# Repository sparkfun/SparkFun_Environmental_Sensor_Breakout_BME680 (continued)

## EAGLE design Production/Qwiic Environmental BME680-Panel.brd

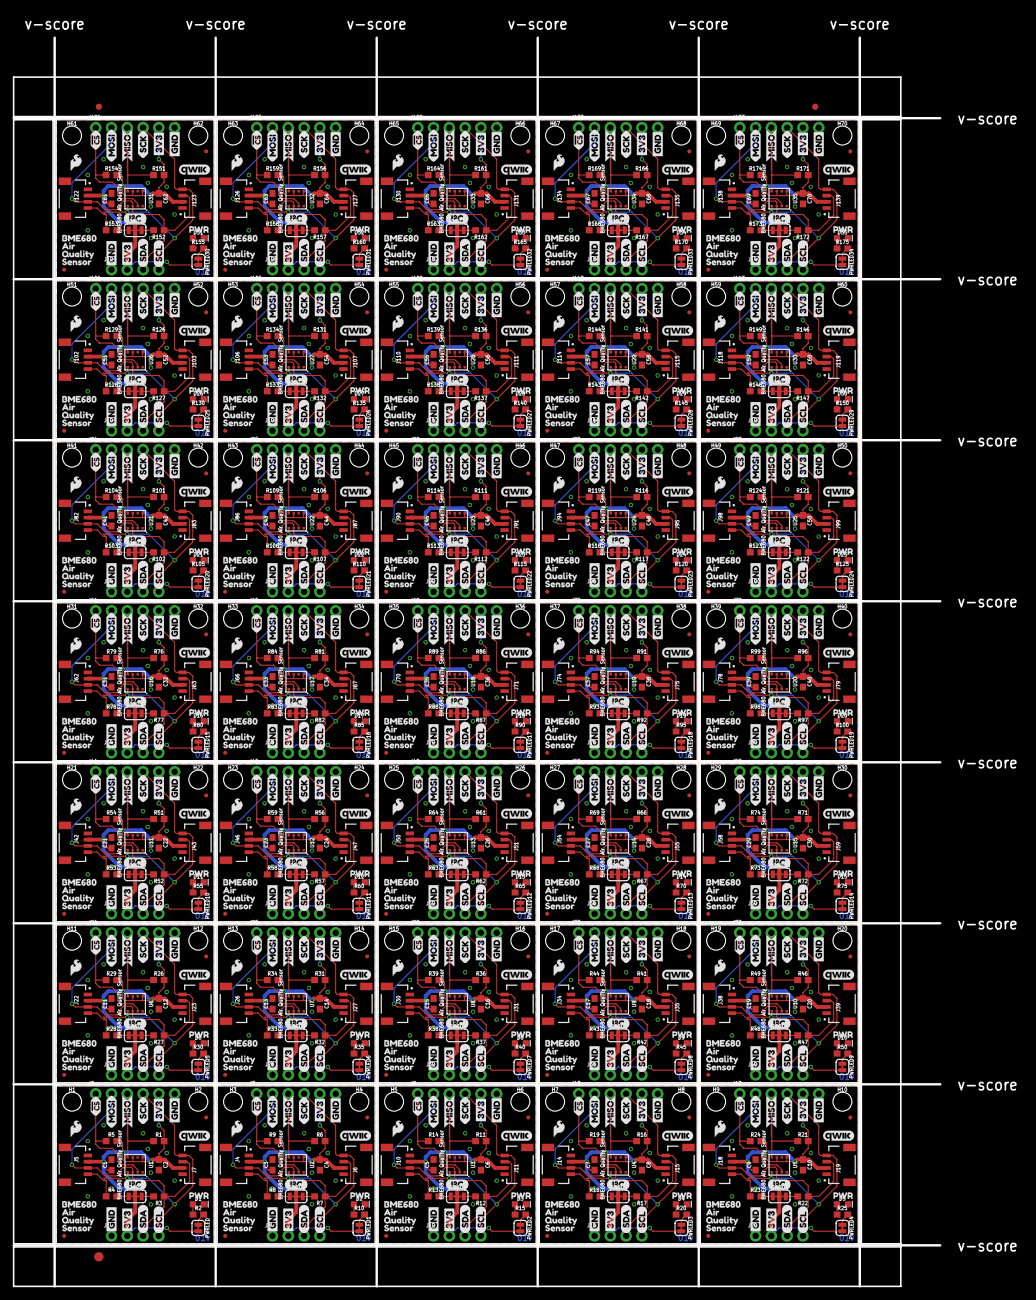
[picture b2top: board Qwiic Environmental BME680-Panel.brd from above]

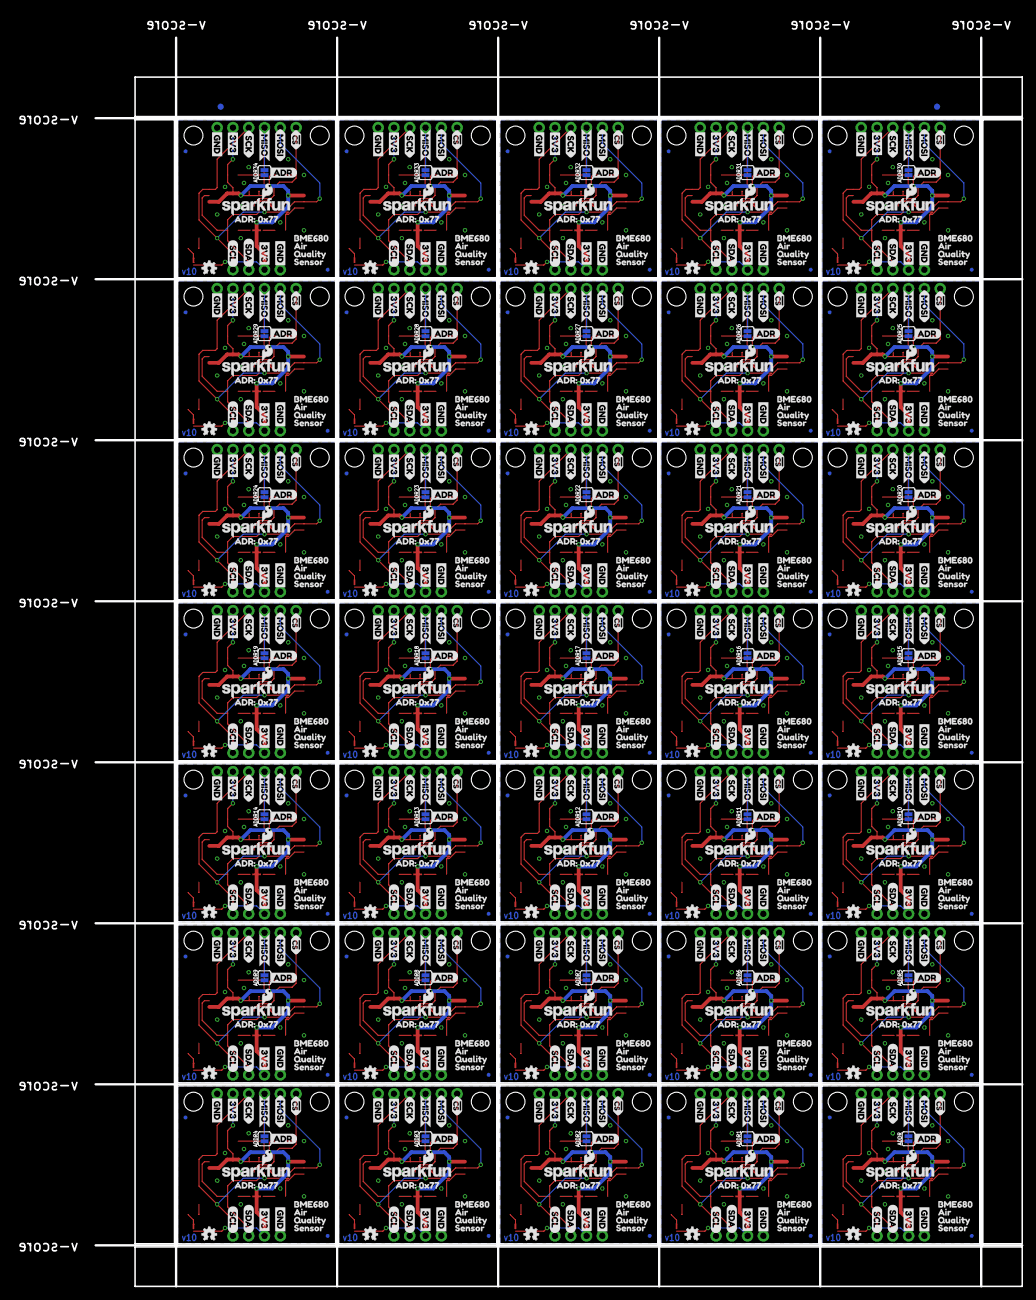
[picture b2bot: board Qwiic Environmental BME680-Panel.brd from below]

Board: 2 copper layers, 149.1 x 200.9 mm, 2070 parts (737 on the bottom side), 350 nets.

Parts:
ADDR, ADDR1, ADDR2, ADDR3, ADDR4, ADDR5, ADDR6, ADDR7, ADDR8, ADDR9, ADDR10, ADDR11, ADDR12, ADDR13, ADDR14, ADDR15, ADDR16, ADDR17, ADDR18, ADDR19, ADDR20, ADDR21, ADDR22, ADDR23, ADDR24, ADDR25, ADDR26, ADDR27, ADDR28, ADDR29, ADDR30, ADDR31, ADDR32, ADDR33, ADDR34: JUMPER-SMT_2_NO_SILK; SMT-JUMPER_2_NO_SILK
C1, C2, C3, C4, C5, C6, C7, C8, C9, C10, C11, C12, C13, C14, C15, C16, C17, C18, C19, C20, C21, C22, C23, C24, C25, C26, C27, C28, C29, C30, C31, C32, C33, C34, C35, C36, C37, C38, C39, C40, C41, C42, C43, C44, C45, C46, C47, C48, C49, C50, C51, C52, C53, C54, C55, C56, C57, C58, C59, C60, C61, C62, C63, C64, C65, C66, C67, C68, C69, C70: 0.1uF; 0603
D1, D2, D3, D4, D5, D6, D7, D8, D9, D10, D11, D12, D13, D14, D15, D16, D17, D18, D19, D20, D21, D22, D23, D24, D25, D26, D27, D28, D29, D30, D31, D32, D33, D34, D35: RED; LED-0603
E$1, E$2, E$3, E$4: FIDUCIAL-1X2
E$5: FIDUCIAL-1.5X3
FD1, FD2, FD3, FD4, FD5, FD6, FD7, FD8, FD9, FD10, FD11, FD12, FD13, FD14, FD15, FD16, FD17, FD18, FD19, FD20, FD21, FD22, FD23, FD24, FD25, FD26, FD27, FD28, FD29, FD30, FD31, FD32, FD33, FD34, FD35, FD36, FD37, FD38, FD39, FD40, FD41, FD42, FD43, FD44, FD45, FD46, FD47, FD48, FD49, FD50, FD51, FD52, FD53, FD54, FD55, FD56, FD57, FD58, FD59, FD60, FD61, FD62, FD63, FD64, FD65, FD66, FD67, FD68, FD69, FD70, FD71, FD72, FD73, FD74, FD75, FD76, FD77, FD78, FD79, FD80, FD81, FD82, FD83, FD84, FD85, FD86, FD87, FD88, FD89, FD90, FD91, FD92, FD93, FD94, FD95, FD96, FD97, FD98, FD99, FD100, FD101, FD102, FD103, FD104, FD105, FD106, FD107, FD108, FD109, FD110, FD111, FD112, FD113, FD114, FD115, FD116, FD117, FD118, FD119, FD120, FD121, FD122, FD123, FD124, FD125, FD126, FD127, FD128, FD129, FD130, FD131, FD132, FD133, FD134, FD135, FD136, FD137, FD138, FD139, FD140: FIDUCIALUFIDUCIAL; FIDUCIAL-MICRO
H1, H2, H3, H4, H5, H6, H7, H8, H9, H10, H11, H12, H13, H14, H15, H16, H17, H18, H19, H20, H21, H22, H23, H24, H25, H26, H27, H28, H29, H30, H31, H32, H33, H34, H35, H36, H37, H38, H39, H40, H41, H42, H43, H44, H45, H46, H47, H48, H49, H50, H51, H52, H53, H54, H55, H56, H57, H58, H59, H60, H61, H62, H63, H64, H65, H66, H67, H68, H69, H70: STAND-OFFTIGHT; STAND-OFF-TIGHT
I2CPU, I2CPU1, I2CPU2, I2CPU3, I2CPU4, I2CPU5, I2CPU6, I2CPU7, I2CPU8, I2CPU9, I2CPU10, I2CPU11, I2CPU12, I2CPU13, I2CPU14, I2CPU15, I2CPU16, I2CPU17, I2CPU18, I2CPU19, I2CPU20, I2CPU21, I2CPU22, I2CPU23, I2CPU24, I2CPU25, I2CPU26, I2CPU27, I2CPU28, I2CPU29, I2CPU30, I2CPU31, I2CPU32, I2CPU33, I2CPU34: I2C PU; SMT-JUMPER_3_2-NC_TRACE_SILK
J1, J8, J12, J16, J20, J24, J28, J32, J36, J40, J44, J48, J52, J56, J60, J64, J68, J72, J76, J80, J84, J88, J92, J96, J100, J104, J108, J112, J116, J120, J124, J128, J132, J136, J140: I2C; 1X04_NO_SILK
J2, J3, J9, J13, J17, J21, J25, J29, J33, J37, J41, J45, J49, J53, J57, J61, J65, J69, J73, J77, J81, J85, J89, J93, J97, J101, J105, J109, J113, J117, J121, J125, J129, J133, J137: SPI; 1X06_NO_SILK
J4, J5, J6, J7, J10, J11, J14, J15, J18, J19, J22, J23, J26, J27, J30, J31, J34, J35, J38, J39, J42, J43, J46, J47, J50, J51, J54, J55, J58, J59, J62, J63, J66, J67, J70, J71, J74, J75, J78, J79, J82, J83, J86, J87, J90, J91, J94, J95, J98, J99, J102, J103, J106, J107, J110, J111, J114, J115, J118, J119, J122, J123, J126, J127, J130, J131, J134, J135, J138, J139: QWIIC; JST04_1MM_RA
LOGO1, LOGO5, LOGO9, LOGO13, LOGO17, LOGO21, LOGO25, LOGO29, LOGO33, LOGO37, LOGO41, LOGO45, LOGO49, LOGO53, LOGO57, LOGO61, LOGO65, LOGO69, LOGO73, LOGO77, LOGO81, LOGO85, LOGO89, LOGO93, LOGO97, LOGO101, LOGO105, LOGO109, LOGO113, LOGO117, LOGO121, LOGO125, LOGO129, LOGO133, LOGO137: OSHW-LOGOMINI; OSHW-LOGO-MINI
LOGO2, LOGO7, LOGO11, LOGO15, LOGO19, LOGO23, LOGO27, LOGO31, LOGO35, LOGO39, LOGO43, LOGO47, LOGO51, LOGO55, LOGO59, LOGO63, LOGO67, LOGO71, LOGO75, LOGO79, LOGO83, LOGO87, LOGO91, LOGO95, LOGO99, LOGO103, LOGO107, LOGO111, LOGO115, LOGO119, LOGO123, LOGO127, LOGO131, LOGO135, LOGO139: SFE_LOGO_NAME_FLAME.1_INCH; SFE_LOGO_NAME_FLAME_.1
LOGO3, LOGO6, LOGO10, LOGO14, LOGO18, LOGO22, LOGO26, LOGO30, LOGO34, LOGO38, LOGO42, LOGO46, LOGO50, LOGO54, LOGO58, LOGO62, LOGO66, LOGO70, LOGO74, LOGO78, LOGO82, LOGO86, LOGO90, LOGO94, LOGO98, LOGO102, LOGO106, LOGO110, LOGO114, LOGO118, LOGO122, LOGO126, LOGO130, LOGO134, LOGO138: REVISION
LOGO4, LOGO8, LOGO12, LOGO16, LOGO20, LOGO24, LOGO28, LOGO32, LOGO36, LOGO40, LOGO44, LOGO48, LOGO52, LOGO56, LOGO60, LOGO64, LOGO68, LOGO72, LOGO76, LOGO80, LOGO84, LOGO88, LOGO92, LOGO96, LOGO100, LOGO104, LOGO108, LOGO112, LOGO116, LOGO120, LOGO124, LOGO128, LOGO132, LOGO136, LOGO140: SFE_LOGO_FLAME.1_INCH; SFE_LOGO_FLAME_.1
PWRLED, PWRLED1, PWRLED2, PWRLED3, PWRLED4, PWRLED5, PWRLED6, PWRLED7, PWRLED8, PWRLED9, PWRLED10, PWRLED11, PWRLED12, PWRLED13, PWRLED14, PWRLED15, PWRLED16, PWRLED17, PWRLED18, PWRLED19, PWRLED20, PWRLED21, PWRLED22, PWRLED23, PWRLED24, PWRLED25, PWRLED26, PWRLED27, PWRLED28, PWRLED29, PWRLED30, PWRLED31, PWRLED32, PWRLED33, PWRLED34: JUMPER-SMT_2_NC_TRACE_SILK; SMT-JUMPER_2_NC_TRACE_SILK
R1, R3, R4, R5, R6, R7, R8, R9, R11, R12, R13, R14, R16, R17, R18, R19, R21, R22, R23, R24, R26, R27, R28, R29, R31, R32, R33, R34, R36, R37, R38, R39, R41, R42, R43, R44, R46, R47, R48, R49, R51, R52, R53, R54, R56, R57, R58, R59, R61, R62, R63, R64, R66, R67, R68, R69, R71, R72, R73, R74, R76, R77, R78, R79, R81, R82, R83, R84, R86, R87, R88, R89, R91, R92, R93, R94, R96, R97, R98, R99, R101, R102, R103, R104, R106, R107, R108, R109, R111, R112, R113, R114, R116, R117, R118, R119, R121, R122, R123, R124, R126, R127, R128, R129, R131, R132, R133, R134, R136, R137, R138, R139, R141, R142, R143, R144, R146, R147, R148, R149, R151, R152, R153, R154, R156, R157, R158, R159, R161, R162, R163, R164, R166, R167, R168, R169, R171, R172, R173, R174: 4.7k; 0603@1
R2, R10, R15, R20, R25, R30, R35, R40, R45, R50, R55, R60, R65, R70, R75, R80, R85, R90, R95, R100, R105, R110, R115, R120, R125, R130, R135, R140, R145, R150, R155, R160, R165, R170, R175: 1k; 0603
U1, U2, U3, U4, U5, U6, U7, U8, U9, U10, U11, U12, U13, U14, U15, U16, U17, U18, U19, U20, U21, U22, U23, U24, U25, U26, U27, U28, U29, U30, U31, U32, U33, U34, U35: BME680 Air Quality Sensor; LGA3.0X3.0
U$1, U$2, U$38, U$39, U$71, U$72, U$104, U$105, U$137, U$138, U$170, U$171, U$203, U$204, U$236, U$237, U$269, U$270, U$302, U$303, U$335, U$336, U$368, U$369, U$401, U$402, U$434, U$435, U$467, U$468, U$500, U$501, U$533, U$534, U$566, U$567, U$599, U$600, U$632, U$633, U$665, U$666, U$698, U$699, U$731, U$732, U$764, U$765, U$797, U$798, U$830, U$831, U$863, U$864, U$896, U$897, U$929, U$930, U$962, U$963, U$995, U$996, U$1028, U$1029, U$1061, U$1062, U$1094, U$1095, U$1127, U$1128: MISO_O
U$3, U$4, U$31, U$35, U$67, U$68, U$100, U$101, U$133, U$134, U$166, U$167, U$199, U$200, U$232, U$233, U$265, U$266, U$298, U$299, U$331, U$332, U$364, U$365, U$397, U$398, U$430, U$431, U$463, U$464, U$496, U$497, U$529, U$530, U$562, U$563, U$595, U$596, U$628, U$629, U$661, U$662, U$694, U$695, U$727, U$728, U$760, U$761, U$793, U$794, U$826, U$827, U$859, U$860, U$892, U$893, U$925, U$926, U$958, U$959, U$991, U$992, U$1024, U$1025, U$1057, U$1058, U$1090, U$1091, U$1123, U$1124: !CS_I
U$5, U$6, U$36, U$37, U$69, U$70, U$102, U$103, U$135, U$136, U$168, U$169, U$201, U$202, U$234, U$235, U$267, U$268, U$300, U$301, U$333, U$334, U$366, U$367, U$399, U$400, U$432, U$433, U$465, U$466, U$498, U$499, U$531, U$532, U$564, U$565, U$597, U$598, U$630, U$631, U$663, U$664, U$696, U$697, U$729, U$730, U$762, U$763, U$795, U$796, U$828, U$829, U$861, U$862, U$894, U$895, U$927, U$928, U$960, U$961, U$993, U$994, U$1026, U$1027, U$1059, U$1060, U$1092, U$1093, U$1125, U$1126: MOSI_I
U$7, U$8, U$40, U$41, U$73, U$74, U$106, U$107, U$139, U$140, U$172, U$173, U$205, U$206, U$238, U$239, U$271, U$272, U$304, U$305, U$337, U$338, U$370, U$371, U$403, U$404, U$436, U$437, U$469, U$470, U$502, U$503, U$535, U$536, U$568, U$569, U$601, U$602, U$634, U$635, U$667, U$668, U$700, U$701, U$733, U$734, U$766, U$767, U$799, U$800, U$832, U$833, U$865, U$866, U$898, U$899, U$931, U$932, U$964, U$965, U$997, U$998, U$1030, U$1031, U$1063, U$1064, U$1096, U$1097, U$1129, U$1130: SCK_I
U$9, U$10, U$16, U$17, U$42, U$43, U$49, U$50, U$75, U$76, U$82, U$83, U$108, U$109, U$115, U$116, U$141, U$142, U$148, U$149, U$174, U$175, U$181, U$182, U$207, U$208, U$214, U$215, U$240, U$241, U$247, U$248, U$273, U$274, U$280, U$281, U$306, U$307, U$313, U$314, U$339, U$340, U$346, U$347, U$372, U$373, U$379, U$380, U$405, U$406, U$412, U$413, U$438, U$439, U$445, U$446, U$471, U$472, U$478, U$479, U$504, U$505, U$511, U$512, U$537, U$538, U$544, U$545, U$570, U$571, U$577, U$578, U$603, U$604, U$610, U$611, U$636, U$637, U$643, U$644, U$669, U$670, U$676, U$677, U$702, U$703, U$709, U$710, U$735, U$736, U$742, U$743, U$768, U$769, U$775, U$776, U$801, U$802, U$808, U$809, U$834, U$835, U$841, U$842, U$867, U$868, U$874, U$875, U$900, U$901, U$907, U$908, U$933, U$934, U$940, U$941, U$966, U$967, U$973, U$974, U$999, U$1000, U$1006, U$1007, U$1032, U$1033, U$1039, U$1040, U$1065, U$1066, U$1072, U$1073, U$1098, U$1099, U$1105, U$1106, U$1131, U$1132, U$1138, U$1139: 3V3_P
U$11, U$12, U$13, U$14, U$44, U$45, U$46, U$47, U$77, U$78, U$79, U$80, U$110, U$111, U$112, U$113, U$143, U$144, U$145, U$146, U$176, U$177, U$178, U$179, U$209, U$210, U$211, U$212, U$242, U$243, U$244, U$245, U$275, U$276, U$277, U$278, U$308, U$309, U$310, U$311, U$341, U$342, U$343, U$344, U$374, U$375, U$376, U$377, U$407, U$408, U$409, U$410, U$440, U$441, U$442, U$443, U$473, U$474, U$475, U$476, U$506, U$507, U$508, U$509, U$539, U$540, U$541, U$542, U$572, U$573, U$574, U$575, U$605, U$606, U$607, U$608, U$638, U$639, U$640, U$641, U$671, U$672, U$673, U$674, U$704, U$705, U$706, U$707, U$737, U$738, U$739, U$740, U$770, U$771, U$772, U$773, U$803, U$804, U$805, U$806, U$836, U$837, U$838, U$839, U$869, U$870, U$871, U$872, U$902, U$903, U$904, U$905, U$935, U$936, U$937, U$938, U$968, U$969, U$970, U$971, U$1001, U$1002, U$1003, U$1004, U$1034, U$1035, U$1036, U$1037, U$1067, U$1068, U$1069, U$1070, U$1100, U$1101, U$1102, U$1103, U$1133, U$1134, U$1135, U$1136: GND_P
U$15, U$48, U$81, U$114, U$147, U$180, U$213, U$246, U$279, U$312, U$345, U$378, U$411, U$444, U$477, U$510, U$543, U$576, U$609, U$642, U$675, U$708, U$741, U$774, U$807, U$840, U$873, U$906, U$939, U$972, U$1005, U$1038, U$1071, U$1104, U$1137: I2C
U$18, U$19, U$51, U$52, U$84, U$85, U$117, U$118, U$150, U$151, U$183, U$184, U$216, U$217, U$249, U$250, U$282, U$283, U$315, U$316, U$348, U$349, U$381, U$382, U$414, U$415, U$447, U$448, U$480, U$481, U$513, U$514, U$546, U$547, U$579, U$580, U$612, U$613, U$645, U$646, U$678, U$679, U$711, U$712, U$744, U$745, U$777, U$778, U$810, U$811, U$843, U$844, U$876, U$877, U$909, U$910, U$942, U$943, U$975, U$976, U$1008, U$1009, U$1041, U$1042, U$1074, U$1075, U$1107, U$1108, U$1140, U$1141: SDA_IO
U$20, U$21, U$53, U$54, U$86, U$87, U$119, U$120, U$152, U$153, U$185, U$186, U$218, U$219, U$251, U$252, U$284, U$285, U$317, U$318, U$350, U$351, U$383, U$384, U$416, U$417, U$449, U$450, U$482, U$483, U$515, U$516, U$548, U$549, U$581, U$582, U$614, U$615, U$647, U$648, U$680, U$681, U$713, U$714, U$746, U$747, U$779, U$780, U$812, U$813, U$845, U$846, U$878, U$879, U$911, U$912, U$944, U$945, U$977, U$978, U$1010, U$1011, U$1043, U$1044, U$1076, U$1077, U$1109, U$1110, U$1142, U$1143: SCL_IO
U$22, U$26, U$55, U$59, U$88, U$92, U$121, U$125, U$154, U$158, U$187, U$191, U$220, U$224, U$253, U$257, U$286, U$290, U$319, U$323, U$352, U$356, U$385, U$389, U$418, U$422, U$451, U$455, U$484, U$488, U$517, U$521, U$550, U$554, U$583, U$587, U$616, U$620, U$649, U$653, U$682, U$686, U$715, U$719, U$748, U$752, U$781, U$785, U$814, U$818, U$847, U$851, U$880, U$884, U$913, U$917, U$946, U$950, U$979, U$983, U$1012, U$1016, U$1045, U$1049, U$1078, U$1082, U$1111, U$1115, U$1144, U$1148: BME6800
U$23, U$27, U$56, U$60, U$89, U$93, U$122, U$126, U$155, U$159, U$188, U$192, U$221, U$225, U$254, U$258, U$287, U$291, U$320, U$324, U$353, U$357, U$386, U$390, U$419, U$423, U$452, U$456, U$485, U$489, U$518, U$522, U$551, U$555, U$584, U$588, U$617, U$621, U$650, U$654, U$683, U$687, U$716, U$720, U$749, U$753, U$782, U$786, U$815, U$819, U$848, U$852, U$881, U$885, U$914, U$918, U$947, U$951, U$980, U$984, U$1013, U$1017, U$1046, U$1050, U$1079, U$1083, U$1112, U$1116, U$1145, U$1149: AIR1
U$24, U$28, U$57, U$61, U$90, U$94, U$123, U$127, U$156, U$160, U$189, U$193, U$222, U$226, U$255, U$259, U$288, U$292, U$321, U$325, U$354, U$358, U$387, U$391, U$420, U$424, U$453, U$457, U$486, U$490, U$519, U$523, U$552, U$556, U$585, U$589, U$618, U$622, U$651, U$655, U$684, U$688, U$717, U$721, U$750, U$754, U$783, U$787, U$816, U$820, U$849, U$853, U$882, U$886, U$915, U$919, U$948, U$952, U$981, U$985, U$1014, U$1018, U$1047, U$1051, U$1080, U$1084, U$1113, U$1117, U$1146, U$1150: QUALITY2
U$25, U$29, U$58, U$62, U$91, U$95, U$124, U$128, U$157, U$161, U$190, U$194, U$223, U$227, U$256, U$260, U$289, U$293, U$322, U$326, U$355, U$359, U$388, U$392, U$421, U$425, U$454, U$458, U$487, U$491, U$520, U$524, U$553, U$557, U$586, U$590, U$619, U$623, U$652, U$656, U$685, U$689, U$718, U$722, U$751, U$755, U$784, U$788, U$817, U$821, U$850, U$854, U$883, U$887, U$916, U$920, U$949, U$953, U$982, U$986, U$1015, U$1019, U$1048, U$1052, U$1081, U$1085, U$1114, U$1118, U$1147, U$1151: SENSOR3
U$30, U$63, U$96, U$129, U$162, U$195, U$228, U$261, U$294, U$327, U$360, U$393, U$426, U$459, U$492, U$525, U$558, U$591, U$624, U$657, U$690, U$723, U$756, U$789, U$822, U$855, U$888, U$921, U$954, U$987, U$1020, U$1053, U$1086, U$1119, U$1152: ADR4
U$32, U$65, U$98, U$131, U$164, U$197, U$230, U$263, U$296, U$329, U$362, U$395, U$428, U$461, U$494, U$527, U$560, U$593, U$626, U$659, U$692, U$725, U$758, U$791, U$824, U$857, U$890, U$923, U$956, U$989, U$1022, U$1055, U$1088, U$1121, U$1154: QWIIC_5MM
U$33, U$64, U$97, U$130, U$163, U$196, U$229, U$262, U$295, U$328, U$361, U$394, U$427, U$460, U$493, U$526, U$559, U$592, U$625, U$658, U$691, U$724, U$757, U$790, U$823, U$856, U$889, U$922, U$955, U$988, U$1021, U$1054, U$1087, U$1120, U$1153: ADR#_0X770
U$34, U$66, U$99, U$132, U$165, U$198, U$231, U$264, U$297, U$330, U$363, U$396, U$429, U$462, U$495, U$528, U$561, U$594, U$627, U$660, U$693, U$726, U$759, U$792, U$825, U$858, U$891, U$924, U$957, U$990, U$1023, U$1056, U$1089, U$1122, U$1155: PWR_TO

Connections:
3.3V: C1.1, C2.1, I2CPU.2, J1.2, J2.5, J5.2, J7.2, PWRLED.2, R1.2, R5.2, U1.6, U1.8
3.3V1: C3.1, C4.1, I2CPU1.2, J3.5, J4.2, J6.2, J8.2, PWRLED1.2, R6.2, R9.2, U2.6, U2.8
3.3V2: C5.1, C6.1, I2CPU2.2, J9.5, J10.2, J11.2, J12.2, PWRLED2.2, R11.2, R14.2, U3.6, U3.8
3.3V3: C7.1, C8.1, I2CPU3.2, J13.5, J14.2, J15.2, J16.2, PWRLED3.2, R16.2, R19.2, U4.6, U4.8
3.3V4: C9.1, C10.1, I2CPU4.2, J17.5, J18.2, J19.2, J20.2, PWRLED4.2, R21.2, R24.2, U5.6, U5.8
3.3V5: C11.1, C12.1, I2CPU5.2, J21.5, J22.2, J23.2, J24.2, PWRLED5.2, R26.2, R29.2, U6.6, U6.8
3.3V6: C13.1, C14.1, I2CPU6.2, J25.5, J26.2, J27.2, J28.2, PWRLED6.2, R31.2, R34.2, U7.6, U7.8
3.3V7: C15.1, C16.1, I2CPU7.2, J29.5, J30.2, J31.2, J32.2, PWRLED7.2, R36.2, R39.2, U8.6, U8.8
3.3V8: C17.1, C18.1, I2CPU8.2, J33.5, J34.2, J35.2, J36.2, PWRLED8.2, R41.2, R44.2, U9.6, U9.8
3.3V9: C19.1, C20.1, I2CPU9.2, J37.5, J38.2, J39.2, J40.2, PWRLED9.2, R46.2, R49.2, U10.6, U10.8
3.3V10: C21.1, C22.1, I2CPU10.2, J41.5, J42.2, J43.2, J44.2, PWRLED10.2, R51.2, R54.2, U11.6, U11.8
3.3V11: C23.1, C24.1, I2CPU11.2, J45.5, J46.2, J47.2, J48.2, PWRLED11.2, R56.2, R59.2, U12.6, U12.8
3.3V12: C25.1, C26.1, I2CPU12.2, J49.5, J50.2, J51.2, J52.2, PWRLED12.2, R61.2, R64.2, U13.6, U13.8
3.3V13: C27.1, C28.1, I2CPU13.2, J53.5, J54.2, J55.2, J56.2, PWRLED13.2, R66.2, R69.2, U14.6, U14.8
3.3V14: C29.1, C30.1, I2CPU14.2, J57.5, J58.2, J59.2, J60.2, PWRLED14.2, R71.2, R74.2, U15.6, U15.8
3.3V15: C31.1, C32.1, I2CPU15.2, J61.5, J62.2, J63.2, J64.2, PWRLED15.2, R76.2, R79.2, U16.6, U16.8
3.3V16: C33.1, C34.1, I2CPU16.2, J65.5, J66.2, J67.2, J68.2, PWRLED16.2, R81.2, R84.2, U17.6, U17.8
3.3V17: C35.1, C36.1, I2CPU17.2, J69.5, J70.2, J71.2, J72.2, PWRLED17.2, R86.2, R89.2, U18.6, U18.8
3.3V18: C37.1, C38.1, I2CPU18.2, J73.5, J74.2, J75.2, J76.2, PWRLED18.2, R91.2, R94.2, U19.6, U19.8
3.3V19: C39.1, C40.1, I2CPU19.2, J77.5, J78.2, J79.2, J80.2, PWRLED19.2, R96.2, R99.2, U20.6, U20.8
3.3V20: C41.1, C42.1, I2CPU20.2, J81.5, J82.2, J83.2, J84.2, PWRLED20.2, R101.2, R104.2, U21.6, U21.8
3.3V21: C43.1, C44.1, I2CPU21.2, J85.5, J86.2, J87.2, J88.2, PWRLED21.2, R106.2, R109.2, U22.6, U22.8
3.3V22: C45.1, C46.1, I2CPU22.2, J89.5, J90.2, J91.2, J92.2, PWRLED22.2, R111.2, R114.2, U23.6, U23.8
3.3V23: C47.1, C48.1, I2CPU23.2, J93.5, J94.2, J95.2, J96.2, PWRLED23.2, R116.2, R119.2, U24.6, U24.8
3.3V24: C49.1, C50.1, I2CPU24.2, J97.5, J98.2, J99.2, J100.2, PWRLED24.2, R121.2, R124.2, U25.6, U25.8
3.3V25: C51.1, C52.1, I2CPU25.2, J101.5, J102.2, J103.2, J104.2, PWRLED25.2, R126.2, R129.2, U26.6, U26.8
3.3V26: C53.1, C54.1, I2CPU26.2, J105.5, J106.2, J107.2, J108.2, PWRLED26.2, R131.2, R134.2, U27.6, U27.8
3.3V27: C55.1, C56.1, I2CPU27.2, J109.5, J110.2, J111.2, J112.2, PWRLED27.2, R136.2, R139.2, U28.6, U28.8
3.3V28: C57.1, C58.1, I2CPU28.2, J113.5, J114.2, J115.2, J116.2, PWRLED28.2, R141.2, R144.2, U29.6, U29.8
3.3V29: C59.1, C60.1, I2CPU29.2, J117.5, J118.2, J119.2, J120.2, PWRLED29.2, R146.2, R149.2, U30.6, U30.8
3.3V30: C61.1, C62.1, I2CPU30.2, J121.5, J122.2, J123.2, J124.2, PWRLED30.2, R151.2, R154.2, U31.6, U31.8
3.3V31: C63.1, C64.1, I2CPU31.2, J125.5, J126.2, J127.2, J128.2, PWRLED31.2, R156.2, R159.2, U32.6, U32.8
3.3V32: C65.1, C66.1, I2CPU32.2, J129.5, J130.2, J131.2, J132.2, PWRLED32.2, R161.2, R164.2, U33.6, U33.8
3.3V33: C67.1, C68.1, I2CPU33.2, J133.5, J134.2, J135.2, J136.2, PWRLED33.2, R166.2, R169.2, U34.6, U34.8
3.3V34: C69.1, C70.1, I2CPU34.2, J137.5, J138.2, J139.2, J140.2, PWRLED34.2, R171.2, R174.2, U35.6, U35.8
!CS: J2.1, R5.1, U1.2
!CS1: J3.1, R9.1, U2.2
!CS2: J9.1, R14.1, U3.2
!CS3: J13.1, R19.1, U4.2
!CS4: J17.1, R24.1, U5.2
!CS5: J21.1, R29.1, U6.2
!CS6: J25.1, R34.1, U7.2
!CS7: J29.1, R39.1, U8.2
!CS8: J33.1, R44.1, U9.2
!CS9: J37.1, R49.1, U10.2
!CS10: J41.1, R54.1, U11.2
!CS11: J45.1, R59.1, U12.2
!CS12: J49.1, R64.1, U13.2
!CS13: J53.1, R69.1, U14.2
!CS14: J57.1, R74.1, U15.2
!CS15: J61.1, R79.1, U16.2
!CS16: J65.1, R84.1, U17.2
!CS17: J69.1, R89.1, U18.2
!CS18: J73.1, R94.1, U19.2
!CS19: J77.1, R99.1, U20.2
!CS20: J81.1, R104.1, U21.2
!CS21: J85.1, R109.1, U22.2
!CS22: J89.1, R114.1, U23.2
!CS23: J93.1, R119.1, U24.2
!CS24: J97.1, R124.1, U25.2
!CS25: J101.1, R129.1, U26.2
!CS26: J105.1, R134.1, U27.2
!CS27: J109.1, R139.1, U28.2
!CS28: J113.1, R144.1, U29.2
!CS29: J117.1, R149.1, U30.2
!CS30: J121.1, R154.1, U31.2
!CS31: J125.1, R159.1, U32.2
!CS32: J129.1, R164.1, U33.2
!CS33: J133.1, R169.1, U34.2
!CS34: J137.1, R174.1, U35.2
GND: ADDR.1, C1.2, C2.2, D1.C, J1.1, J2.6, J5.1, J7.1, U1.1, U1.7
GND1: ADDR1.1, C3.2, C4.2, D2.C, J3.6, J4.1, J6.1, J8.1, U2.1, U2.7
GND2: ADDR2.1, C5.2, C6.2, D3.C, J9.6, J10.1, J11.1, J12.1, U3.1, U3.7
GND3: ADDR3.1, C7.2, C8.2, D4.C, J13.6, J14.1, J15.1, J16.1, U4.1, U4.7
GND4: ADDR4.1, C9.2, C10.2, D5.C, J17.6, J18.1, J19.1, J20.1, U5.1, U5.7
GND5: ADDR5.1, C11.2, C12.2, D6.C, J21.6, J22.1, J23.1, J24.1, U6.1, U6.7
GND6: ADDR6.1, C13.2, C14.2, D7.C, J25.6, J26.1, J27.1, J28.1, U7.1, U7.7
GND7: ADDR7.1, C15.2, C16.2, D8.C, J29.6, J30.1, J31.1, J32.1, U8.1, U8.7
GND8: ADDR8.1, C17.2, C18.2, D9.C, J33.6, J34.1, J35.1, J36.1, U9.1, U9.7
GND9: ADDR9.1, C19.2, C20.2, D10.C, J37.6, J38.1, J39.1, J40.1, U10.1, U10.7
GND10: ADDR10.1, C21.2, C22.2, D11.C, J41.6, J42.1, J43.1, J44.1, U11.1, U11.7
GND11: ADDR11.1, C23.2, C24.2, D12.C, J45.6, J46.1, J47.1, J48.1, U12.1, U12.7
GND12: ADDR12.1, C25.2, C26.2, D13.C, J49.6, J50.1, J51.1, J52.1, U13.1, U13.7
GND13: ADDR13.1, C27.2, C28.2, D14.C, J53.6, J54.1, J55.1, J56.1, U14.1, U14.7
GND14: ADDR14.1, C29.2, C30.2, D15.C, J57.6, J58.1, J59.1, J60.1, U15.1, U15.7
GND15: ADDR15.1, C31.2, C32.2, D16.C, J61.6, J62.1, J63.1, J64.1, U16.1, U16.7
GND16: ADDR16.1, C33.2, C34.2, D17.C, J65.6, J66.1, J67.1, J68.1, U17.1, U17.7
GND17: ADDR17.1, C35.2, C36.2, D18.C, J69.6, J70.1, J71.1, J72.1, U18.1, U18.7
GND18: ADDR18.1, C37.2, C38.2, D19.C, J73.6, J74.1, J75.1, J76.1, U19.1, U19.7
GND19: ADDR19.1, C39.2, C40.2, D20.C, J77.6, J78.1, J79.1, J80.1, U20.1, U20.7
GND20: ADDR20.1, C41.2, C42.2, D21.C, J81.6, J82.1, J83.1, J84.1, U21.1, U21.7
GND21: ADDR21.1, C43.2, C44.2, D22.C, J85.6, J86.1, J87.1, J88.1, U22.1, U22.7
GND22: ADDR22.1, C45.2, C46.2, D23.C, J89.6, J90.1, J91.1, J92.1, U23.1, U23.7
GND23: ADDR23.1, C47.2, C48.2, D24.C, J93.6, J94.1, J95.1, J96.1, U24.1, U24.7
GND24: ADDR24.1, C49.2, C50.2, D25.C, J97.6, J98.1, J99.1, J100.1, U25.1, U25.7
GND25: ADDR25.1, C51.2, C52.2, D26.C, J101.6, J102.1, J103.1, J104.1, U26.1, U26.7
GND26: ADDR26.1, C53.2, C54.2, D27.C, J105.6, J106.1, J107.1, J108.1, U27.1, U27.7
GND27: ADDR27.1, C55.2, C56.2, D28.C, J109.6, J110.1, J111.1, J112.1, U28.1, U28.7
GND28: ADDR28.1, C57.2, C58.2, D29.C, J113.6, J114.1, J115.1, J116.1, U29.1, U29.7
GND29: ADDR29.1, C59.2, C60.2, D30.C, J117.6, J118.1, J119.1, J120.1, U30.1, U30.7
GND30: ADDR30.1, C61.2, C62.2, D31.C, J121.6, J122.1, J123.1, J124.1, U31.1, U31.7
GND31: ADDR31.1, C63.2, C64.2, D32.C, J125.6, J126.1, J127.1, J128.1, U32.1, U32.7
GND32: ADDR32.1, C65.2, C66.2, D33.C, J129.6, J130.1, J131.1, J132.1, U33.1, U33.7
GND33: ADDR33.1, C67.2, C68.2, D34.C, J133.6, J134.1, J135.1, J136.1, U34.1, U34.7
GND34: ADDR34.1, C69.2, C70.2, D35.C, J137.6, J138.1, J139.1, J140.1, U35.1, U35.7
unnamed: PWRLED.1, R2.2
unnamed: I2CPU1.3, R7.2
unnamed: D1.A, R2.1
unnamed: I2CPU.3, R3.2
unnamed: I2CPU.1, R4.2
unnamed: I2CPU1.1, R8.2
unnamed: D2.A, R10.1
unnamed: PWRLED1.1, R10.2
unnamed: I2CPU2.3, R12.2
unnamed: I2CPU2.1, R13.2
unnamed: D3.A, R15.1
unnamed: PWRLED2.1, R15.2
unnamed: I2CPU3.3, R17.2
unnamed: I2CPU3.1, R18.2
unnamed: D4.A, R20.1
unnamed: PWRLED3.1, R20.2
unnamed: I2CPU4.3, R22.2
unnamed: I2CPU4.1, R23.2
unnamed: D5.A, R25.1
unnamed: PWRLED4.1, R25.2
unnamed: I2CPU5.3, R27.2
unnamed: I2CPU5.1, R28.2
unnamed: D6.A, R30.1
unnamed: PWRLED5.1, R30.2
unnamed: I2CPU6.3, R32.2
unnamed: I2CPU6.1, R33.2
unnamed: D7.A, R35.1
unnamed: PWRLED6.1, R35.2
unnamed: I2CPU7.3, R37.2
unnamed: I2CPU7.1, R38.2
unnamed: D8.A, R40.1
unnamed: PWRLED7.1, R40.2
unnamed: I2CPU8.3, R42.2
unnamed: I2CPU8.1, R43.2
unnamed: D9.A, R45.1
unnamed: PWRLED8.1, R45.2
unnamed: I2CPU9.3, R47.2
unnamed: I2CPU9.1, R48.2
unnamed: D10.A, R50.1
unnamed: PWRLED9.1, R50.2
unnamed: I2CPU10.3, R52.2
unnamed: I2CPU10.1, R53.2
unnamed: D11.A, R55.1
unnamed: PWRLED10.1, R55.2
unnamed: I2CPU11.3, R57.2
unnamed: I2CPU11.1, R58.2
unnamed: D12.A, R60.1
unnamed: PWRLED11.1, R60.2
unnamed: I2CPU12.3, R62.2
unnamed: I2CPU12.1, R63.2
unnamed: D13.A, R65.1
unnamed: PWRLED12.1, R65.2
unnamed: I2CPU13.3, R67.2
unnamed: I2CPU13.1, R68.2
unnamed: D14.A, R70.1
unnamed: PWRLED13.1, R70.2
unnamed: I2CPU14.3, R72.2
unnamed: I2CPU14.1, R73.2
unnamed: D15.A, R75.1
unnamed: PWRLED14.1, R75.2
unnamed: I2CPU15.3, R77.2
unnamed: I2CPU15.1, R78.2
unnamed: D16.A, R80.1
unnamed: PWRLED15.1, R80.2
unnamed: I2CPU16.3, R82.2
unnamed: I2CPU16.1, R83.2
unnamed: D17.A, R85.1
unnamed: PWRLED16.1, R85.2
unnamed: I2CPU17.3, R87.2
unnamed: I2CPU17.1, R88.2
unnamed: D18.A, R90.1
unnamed: PWRLED17.1, R90.2
unnamed: I2CPU18.3, R92.2
unnamed: I2CPU18.1, R93.2
unnamed: D19.A, R95.1
unnamed: PWRLED18.1, R95.2
unnamed: I2CPU19.3, R97.2
unnamed: I2CPU19.1, R98.2
unnamed: D20.A, R100.1
unnamed: PWRLED19.1, R100.2
unnamed: I2CPU20.3, R102.2
unnamed: I2CPU20.1, R103.2
unnamed: D21.A, R105.1
unnamed: PWRLED20.1, R105.2
unnamed: I2CPU21.3, R107.2
unnamed: I2CPU21.1, R108.2
unnamed: D22.A, R110.1
unnamed: PWRLED21.1, R110.2
unnamed: I2CPU22.3, R112.2
unnamed: I2CPU22.1, R113.2
unnamed: D23.A, R115.1
unnamed: PWRLED22.1, R115.2
unnamed: I2CPU23.3, R117.2
unnamed: I2CPU23.1, R118.2
unnamed: D24.A, R120.1
unnamed: PWRLED23.1, R120.2
unnamed: I2CPU24.3, R122.2
unnamed: I2CPU24.1, R123.2
unnamed: D25.A, R125.1
unnamed: PWRLED24.1, R125.2
unnamed: I2CPU25.3, R127.2
unnamed: I2CPU25.1, R128.2
unnamed: D26.A, R130.1
unnamed: PWRLED25.1, R130.2
unnamed: I2CPU26.3, R132.2
unnamed: I2CPU26.1, R133.2
unnamed: D27.A, R135.1
unnamed: PWRLED26.1, R135.2
unnamed: I2CPU27.3, R137.2
unnamed: I2CPU27.1, R138.2
unnamed: D28.A, R140.1
unnamed: PWRLED27.1, R140.2
unnamed: I2CPU28.3, R142.2
unnamed: I2CPU28.1, R143.2
unnamed: D29.A, R145.1
unnamed: PWRLED28.1, R145.2
unnamed: I2CPU29.3, R147.2
unnamed: I2CPU29.1, R148.2
unnamed: D30.A, R150.1
unnamed: PWRLED29.1, R150.2
unnamed: I2CPU30.3, R152.2
unnamed: I2CPU30.1, R153.2
unnamed: D31.A, R155.1
unnamed: PWRLED30.1, R155.2
unnamed: I2CPU31.3, R157.2
unnamed: I2CPU31.1, R158.2
unnamed: D32.A, R160.1
unnamed: PWRLED31.1, R160.2
unnamed: I2CPU32.3, R162.2
unnamed: I2CPU32.1, R163.2
unnamed: D33.A, R165.1
unnamed: PWRLED32.1, R165.2
unnamed: I2CPU33.3, R167.2
unnamed: I2CPU33.1, R168.2
unnamed: D34.A, R170.1
unnamed: PWRLED33.1, R170.2
unnamed: I2CPU34.3, R172.2
unnamed: I2CPU34.1, R173.2
unnamed: D35.A, R175.1
unnamed: PWRLED34.1, R175.2
SCK/SCL: J1.4, J2.4, J5.4, J7.4, R4.1, U1.4
SCK/SCL1: J3.4, J4.4, J6.4, J8.4, R8.1, U2.4
SCK/SCL2: J9.4, J10.4, J11.4, J12.4, R13.1, U3.4
SCK/SCL3: J13.4, J14.4, J15.4, J16.4, R18.1, U4.4
SCK/SCL4: J17.4, J18.4, J19.4, J20.4, R23.1, U5.4
SCK/SCL5: J21.4, J22.4, J23.4, J24.4, R28.1, U6.4
SCK/SCL6: J25.4, J26.4, J27.4, J28.4, R33.1, U7.4
SCK/SCL7: J29.4, J30.4, J31.4, J32.4, R38.1, U8.4
SCK/SCL8: J33.4, J34.4, J35.4, J36.4, R43.1, U9.4
SCK/SCL9: J37.4, J38.4, J39.4, J40.4, R48.1, U10.4
SCK/SCL10: J41.4, J42.4, J43.4, J44.4, R53.1, U11.4
SCK/SCL11: J45.4, J46.4, J47.4, J48.4, R58.1, U12.4
SCK/SCL12: J49.4, J50.4, J51.4, J52.4, R63.1, U13.4
SCK/SCL13: J53.4, J54.4, J55.4, J56.4, R68.1, U14.4
SCK/SCL14: J57.4, J58.4, J59.4, J60.4, R73.1, U15.4
SCK/SCL15: J61.4, J62.4, J63.4, J64.4, R78.1, U16.4
SCK/SCL16: J65.4, J66.4, J67.4, J68.4, R83.1, U17.4
SCK/SCL17: J69.4, J70.4, J71.4, J72.4, R88.1, U18.4
SCK/SCL18: J73.4, J74.4, J75.4, J76.4, R93.1, U19.4
SCK/SCL19: J77.4, J78.4, J79.4, J80.4, R98.1, U20.4
SCK/SCL20: J81.4, J82.4, J83.4, J84.4, R103.1, U21.4
SCK/SCL21: J85.4, J86.4, J87.4, J88.4, R108.1, U22.4
SCK/SCL22: J89.4, J90.4, J91.4, J92.4, R113.1, U23.4
SCK/SCL23: J93.4, J94.4, J95.4, J96.4, R118.1, U24.4
SCK/SCL24: J97.4, J98.4, J99.4, J100.4, R123.1, U25.4
SCK/SCL25: J101.4, J102.4, J103.4, J104.4, R128.1, U26.4
SCK/SCL26: J105.4, J106.4, J107.4, J108.4, R133.1, U27.4
SCK/SCL27: J109.4, J110.4, J111.4, J112.4, R138.1, U28.4
SCK/SCL28: J113.4, J114.4, J115.4, J116.4, R143.1, U29.4
SCK/SCL29: J117.4, J118.4, J119.4, J120.4, R148.1, U30.4
SCK/SCL30: J121.4, J122.4, J123.4, J124.4, R153.1, U31.4
SCK/SCL31: J125.4, J126.4, J127.4, J128.4, R158.1, U32.4
SCK/SCL32: J129.4, J130.4, J131.4, J132.4, R163.1, U33.4
SCK/SCL33: J133.4, J134.4, J135.4, J136.4, R168.1, U34.4
SCK/SCL34: J137.4, J138.4, J139.4, J140.4, R173.1, U35.4
SDI/SDA: J1.3, J2.2, J5.3, J7.3, R3.1, U1.3
SDI/SDA1: J3.2, J4.3, J6.3, J8.3, R7.1, U2.3
SDI/SDA2: J9.2, J10.3, J11.3, J12.3, R12.1, U3.3
SDI/SDA3: J13.2, J14.3, J15.3, J16.3, R17.1, U4.3
SDI/SDA4: J17.2, J18.3, J19.3, J20.3, R22.1, U5.3
SDI/SDA5: J21.2, J22.3, J23.3, J24.3, R27.1, U6.3
SDI/SDA6: J25.2, J26.3, J27.3, J28.3, R32.1, U7.3
SDI/SDA7: J29.2, J30.3, J31.3, J32.3, R37.1, U8.3
SDI/SDA8: J33.2, J34.3, J35.3, J36.3, R42.1, U9.3
SDI/SDA9: J37.2, J38.3, J39.3, J40.3, R47.1, U10.3
SDI/SDA10: J41.2, J42.3, J43.3, J44.3, R52.1, U11.3
SDI/SDA11: J45.2, J46.3, J47.3, J48.3, R57.1, U12.3
SDI/SDA12: J49.2, J50.3, J51.3, J52.3, R62.1, U13.3
SDI/SDA13: J53.2, J54.3, J55.3, J56.3, R67.1, U14.3
SDI/SDA14: J57.2, J58.3, J59.3, J60.3, R72.1, U15.3
SDI/SDA15: J61.2, J62.3, J63.3, J64.3, R77.1, U16.3
SDI/SDA16: J65.2, J66.3, J67.3, J68.3, R82.1, U17.3
SDI/SDA17: J69.2, J70.3, J71.3, J72.3, R87.1, U18.3
SDI/SDA18: J73.2, J74.3, J75.3, J76.3, R92.1, U19.3
SDI/SDA19: J77.2, J78.3, J79.3, J80.3, R97.1, U20.3
SDI/SDA20: J81.2, J82.3, J83.3, J84.3, R102.1, U21.3
SDI/SDA21: J85.2, J86.3, J87.3, J88.3, R107.1, U22.3
SDI/SDA22: J89.2, J90.3, J91.3, J92.3, R112.1, U23.3
SDI/SDA23: J93.2, J94.3, J95.3, J96.3, R117.1, U24.3
SDI/SDA24: J97.2, J98.3, J99.3, J100.3, R122.1, U25.3
SDI/SDA25: J101.2, J102.3, J103.3, J104.3, R127.1, U26.3
SDI/SDA26: J105.2, J106.3, J107.3, J108.3, R132.1, U27.3
SDI/SDA27: J109.2, J110.3, J111.3, J112.3, R137.1, U28.3
SDI/SDA28: J113.2, J114.3, J115.3, J116.3, R142.1, U29.3
SDI/SDA29: J117.2, J118.3, J119.3, J120.3, R147.1, U30.3
SDI/SDA30: J121.2, J122.3, J123.3, J124.3, R152.1, U31.3
SDI/SDA31: J125.2, J126.3, J127.3, J128.3, R157.1, U32.3
SDI/SDA32: J129.2, J130.3, J131.3, J132.3, R162.1, U33.3
SDI/SDA33: J133.2, J134.3, J135.3, J136.3, R167.1, U34.3
SDI/SDA34: J137.2, J138.3, J139.3, J140.3, R172.1, U35.3
SDO/ADR: ADDR.2, J2.3, R1.1, U1.5
SDO/ADR1: ADDR1.2, J3.3, R6.1, U2.5
SDO/ADR2: ADDR2.2, J9.3, R11.1, U3.5
SDO/ADR3: ADDR3.2, J13.3, R16.1, U4.5
SDO/ADR4: ADDR4.2, J17.3, R21.1, U5.5
SDO/ADR5: ADDR5.2, J21.3, R26.1, U6.5
SDO/ADR6: ADDR6.2, J25.3, R31.1, U7.5
SDO/ADR7: ADDR7.2, J29.3, R36.1, U8.5
SDO/ADR8: ADDR8.2, J33.3, R41.1, U9.5
SDO/ADR9: ADDR9.2, J37.3, R46.1, U10.5
SDO/ADR10: ADDR10.2, J41.3, R51.1, U11.5
SDO/ADR11: ADDR11.2, J45.3, R56.1, U12.5
SDO/ADR12: ADDR12.2, J49.3, R61.1, U13.5
SDO/ADR13: ADDR13.2, J53.3, R66.1, U14.5
SDO/ADR14: ADDR14.2, J57.3, R71.1, U15.5
SDO/ADR15: ADDR15.2, J61.3, R76.1, U16.5
SDO/ADR16: ADDR16.2, J65.3, R81.1, U17.5
SDO/ADR17: ADDR17.2, J69.3, R86.1, U18.5
SDO/ADR18: ADDR18.2, J73.3, R91.1, U19.5
SDO/ADR19: ADDR19.2, J77.3, R96.1, U20.5
SDO/ADR20: ADDR20.2, J81.3, R101.1, U21.5
SDO/ADR21: ADDR21.2, J85.3, R106.1, U22.5
SDO/ADR22: ADDR22.2, J89.3, R111.1, U23.5
SDO/ADR23: ADDR23.2, J93.3, R116.1, U24.5
SDO/ADR24: ADDR24.2, J97.3, R121.1, U25.5
SDO/ADR25: ADDR25.2, J101.3, R126.1, U26.5
SDO/ADR26: ADDR26.2, J105.3, R131.1, U27.5
SDO/ADR27: ADDR27.2, J109.3, R136.1, U28.5
SDO/ADR28: ADDR28.2, J113.3, R141.1, U29.5
SDO/ADR29: ADDR29.2, J117.3, R146.1, U30.5
SDO/ADR30: ADDR30.2, J121.3, R151.1, U31.5
SDO/ADR31: ADDR31.2, J125.3, R156.1, U32.5
SDO/ADR32: ADDR32.2, J129.3, R161.1, U33.5
SDO/ADR33: ADDR33.2, J133.3, R166.1, U34.5
SDO/ADR34: ADDR34.2, J137.3, R171.1, U35.5

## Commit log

2020-03-24 removing exported libraries
2020-03-30 adding buzzard for address
2020-03-31 pre design review changes
2020-03-31 post checklist/review changes
2020-04-01 adding panel
2020-04-28 Create README
    Created README File.
2020-05-13 Update README
    Adding product photo and link to BME680 Arduino Library.
2020-05-14 cleaning repo
